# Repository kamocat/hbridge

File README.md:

# hbridge
A discrete h-bridge for DC motor control

## Features
- 20V operation
- Up to 500kHz switch frequency
- 600ns turn-on time
- 150ns turn-off time

## Scope captures

## References
[MOSFET driver primer](https://www.ti.com/lit/ml/slua618a/slua618a.pdf)

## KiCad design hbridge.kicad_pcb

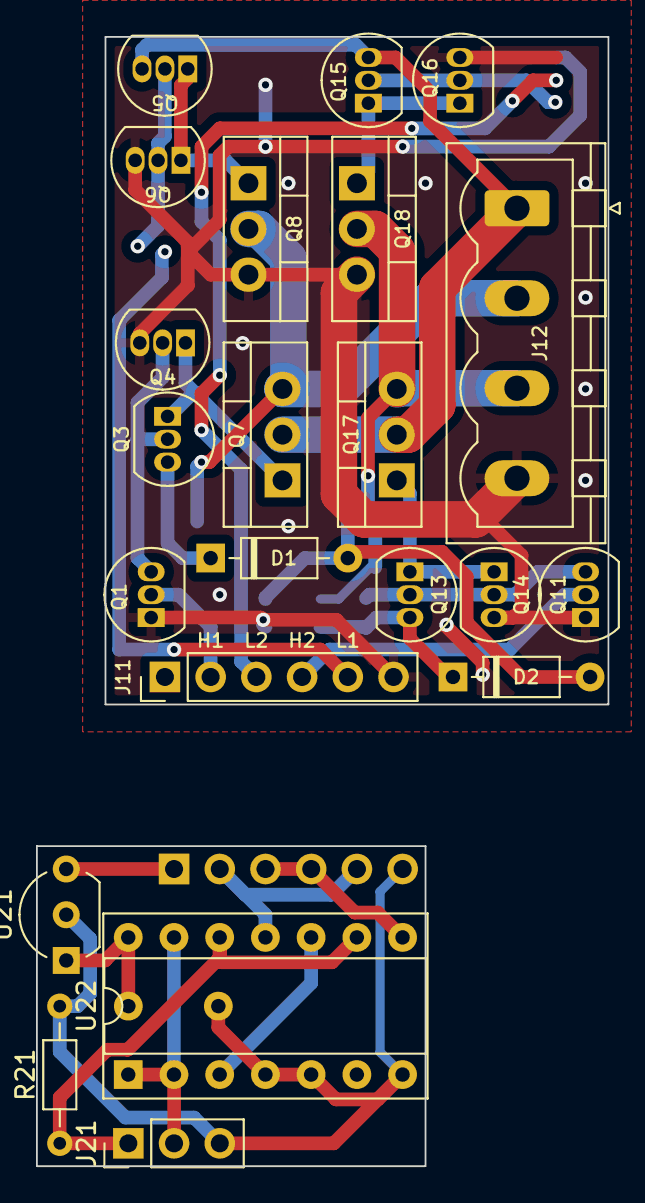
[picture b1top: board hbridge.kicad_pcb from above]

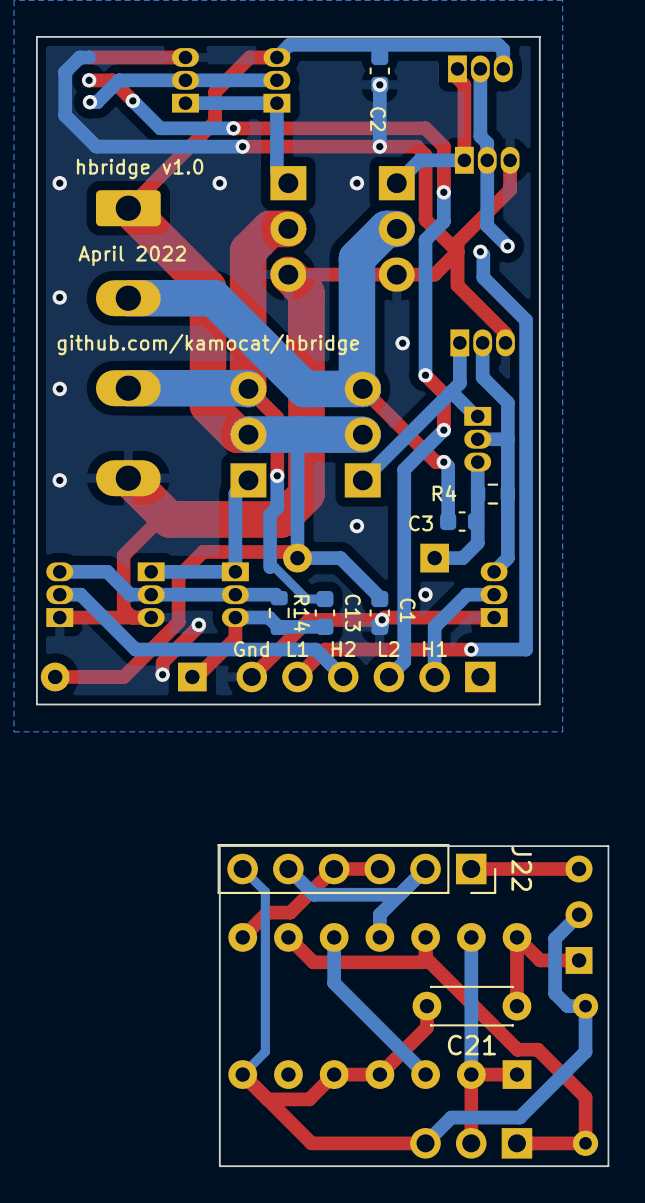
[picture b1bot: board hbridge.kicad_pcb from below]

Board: 4 copper layers, 31.8 x 62.7 mm, 30 parts (8 on the bottom side), 18 nets.

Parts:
C1, C2, C3, C13: 1u; C_0603_1608Metric
C21: 0.1u; C_Disc_D4.3mm_W1.9mm_P5.00mm
D1, D2: 1N4148; D_DO-35_SOD27_P7.62mm_Horizontal
J11: Conn_01x06_Male; PinHeader_1x06_P2.54mm_Vertical
J12: Screw_Terminal_01x04; PhoenixContact_MSTBVA_2,5_4-G_1x04_P5.00mm_Vertical
J21: Conn_01x03_Male; PinHeader_1x03_P2.54mm_Vertical
J22: Conn_01x06_Female; PinSocket_1x06_P2.54mm_Vertical
Q1, Q11: 2N7000; TO-92_Inline
Q3, Q5, Q13, Q15: 2N3904; TO-92_Inline
Q4, Q6, Q14, Q16: 2N3906; TO-92_Inline
Q7, Q8, Q17, Q18: STP20NF06; TO-220-3_Vertical
R4, R14: 10k; R_0603_1608Metric
R21: 10k; R_Axial_DIN0204_L3.6mm_D1.6mm_P7.62mm_Horizontal
U21: LM78L05_TO92; TO-92_Inline_Wide
U22: 74HC00; DIP-14_W7.62mm_Socket

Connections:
+5V: C21.1, U21.1 (VO), U22.14 (VCC)
+12V: C1.1, C2.1, D1.2 (A), D2.2 (A), J11.1, J12.1, J22.1, Q5.3 (C), Q7.2 (D), Q15.3 (C), Q17.2 (D), U21.3 (VI)
/DIR: J21.2, U22.1, U22.2, U22.13
/EN: J21.1, R21.1, U22.9, U22.12
/H1: J11.2, J11.5, J22.2, J22.5, Q1.2 (G), Q5.2 (B), Q6.2 (B), U22.11
/H2: J11.3, J11.4, J22.3, J22.4, Q11.2 (G), Q15.2 (B), Q16.2 (B), U22.8
/OUT1: C3.2, J12.2, Q7.3 (S), Q8.2 (D)
/OUT2: C13.2, J12.3, Q17.3 (S), Q18.2 (D)
/boot1: C3.1, D1.1 (K), Q3.3 (C), R4.1
/boot2: C13.1, D2.1 (K), Q13.3 (C), R14.1
/drvH1: Q3.1 (E), Q4.1 (E), Q7.1 (G)
/drvH2: Q13.1 (E), Q14.1 (E), Q17.1 (G)
/drvL1: Q5.1 (E), Q6.1 (E), Q8.1 (G)
/drvL2: Q15.1 (E), Q16.1 (E), Q18.1 (G)
GND: C1.2, C2.2, C21.2, J11.6, J12.4, J21.3, J22.6, Q1.1 (S), Q4.3 (C), Q6.3 (C), Q8.3 (S), Q11.1 (S), Q14.3 (C), Q16.3 (C), Q18.3 (S), R21.2, U21.2 (GND), U22.4, U22.5, U22.7 (GND)
unnamed: Q1.3 (D), Q3.2 (B), Q4.2 (B), R4.2
unnamed: Q11.3 (D), Q13.2 (B), Q14.2 (B), R14.2
unnamed: U22.3, U22.10

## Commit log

2022-02-24 Created half-bridge for testing
2022-04-06 Removed backup files
2022-04-06 Improved proto layout, snapped to 100 mil
2022-04-07 Reduce layout to 1x1 inch, cleaned up silkscreen
2022-04-10 Reduced the unique parts count by consolidating resistors and capacitors
2022-04-11 Tied Q4 collector to ground to turn off Q7 harder. Moved traces so entire back side is ground plane.
2022-04-13 Removed R3 to turn off Q7 harder
2022-04-13 Added second half-bridge to make h-bridge. Not routed yet
2022-04-14 More compact layout using smd resistors and capacitors
2022-04-14 Switched diodes to smd
2022-04-14 Switched out diodes for more common parts
2022-04-14 Routed traces
2022-04-14 Finished sikscreen
2022-04-14 Finishing touches, sent off to fab
2022-04-15 Added logic to simplify control
2022-04-15 Used internal layer to show redlines
2022-04-15 Added bypass cap, tied unused inputs to gnd
2022-08-24 Rerouted greenwires
    Found a simpler way to modify board
2022-08-24 Added photos
